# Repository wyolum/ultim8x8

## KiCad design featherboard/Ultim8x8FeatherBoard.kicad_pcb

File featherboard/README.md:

An add-on board to the Ultim8x8 LED Matrix for mounting an Adafruit Feather 
Huzzah (ESP8266).

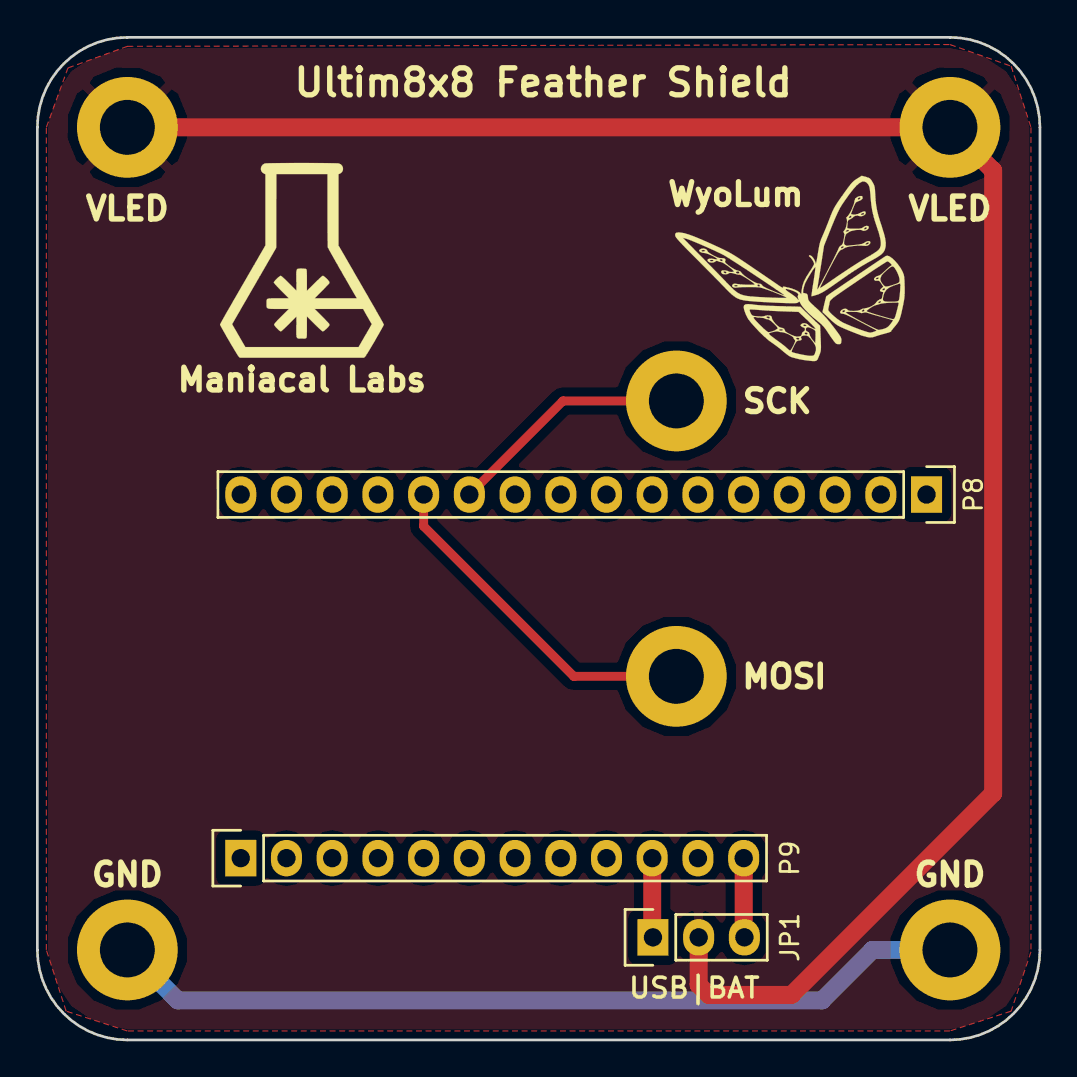
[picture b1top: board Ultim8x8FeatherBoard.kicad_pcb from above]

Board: 2 copper layers, 55.7 x 55.7 mm, 11 parts (0 on the bottom side), 6 nets.

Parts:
JP1: JUMPER3; Pin_Header_Straight_1x03
P1: Maniacal Labs; logo_MLlabs
P2, P3: VLED; Screw
P4, P5: GND; Screw
P6: MOSI; Screw
P7: SCK; Screw
P8: CONN_01X16; Pin_Header_Straight_1x16
P9: CONN_01X12; Pin_Header_Straight_1x12
P10: WyoLum; logo_wyo_butterfly

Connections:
GND: P4.1, P5.1, P8.4
MOSI: P6.1, P8.12
SCK: P7.1, P8.11
VBAT: JP1.3, P9.12
VLED: JP1.2, P2.1, P3.1
VUSB: JP1.1, P9.10

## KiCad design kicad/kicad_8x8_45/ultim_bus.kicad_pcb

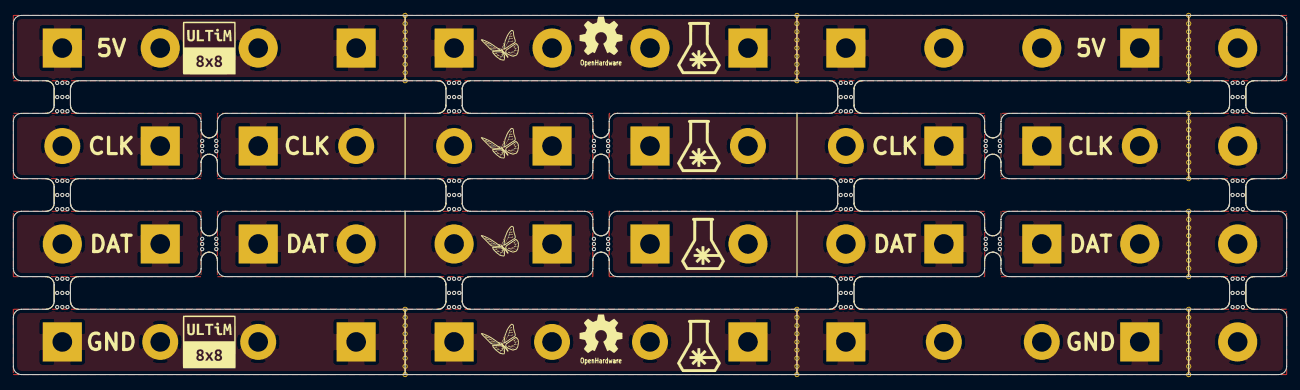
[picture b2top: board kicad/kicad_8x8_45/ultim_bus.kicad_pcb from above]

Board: 2 copper layers, 198.1 x 55.9 mm, 82 parts (0 on the bottom side), 10 nets.

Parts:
L1, L2: OSHW; OSHW_6mm
L3, L4, L5, L6: WyoLum; logo_wyo_butterfly_small
L7, L8, L9, L10: Maniacal; logo_MLlabs_small
L11, L12: ULTiM; logo_ultim8x8_small
M1, M2, M3, M4, M8, M9, M10, M11, M15, M16, M17, M18: MouseBite; mouse-bite-5.08mm-slot
M5, M6, M7, M12, M13, M14: MouseBite; mouse-bite-2.54mm-slot
P1, P4, P5, P8, P9, P12, P15, P16, P19, P20, P23, P24, P28, P29, P32, P33, P36, P37, P40, P43, P44, P47, P48, P51: CONN_1; Screw_SqPad
P2, P3, P6, P7, P10, P11, P13, P14, P17, P18, P21, P22, P25, P26, P27, P30, P31, P34, P35, P38, P39, P41, P42, P45, P46, P49, P50, P52: CONN_1; Screw

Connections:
/ROW1: P1.1, P2.1, P3.1, P4.1, P5.1, P6.1, P7.1, P8.1, P9.1, P10.1, P11.1, P12.1, P13.1
/ROW2: P40.1, P41.1, P42.1, P43.1, P44.1, P45.1, P46.1, P47.1, P48.1, P49.1, P50.1, P51.1, P52.1
/ROW31: P14.1, P15.1
/ROW32: P16.1, P17.1, P18.1, P19.1
/ROW33: P20.1, P21.1, P22.1, P23.1
/ROW34: P24.1, P25.1, P26.1
/ROW41: P27.1, P28.1
/ROW42: P29.1, P30.1, P31.1, P32.1
/ROW43: P33.1, P34.1, P35.1, P36.1
/ROW44: P37.1, P38.1, P39.1

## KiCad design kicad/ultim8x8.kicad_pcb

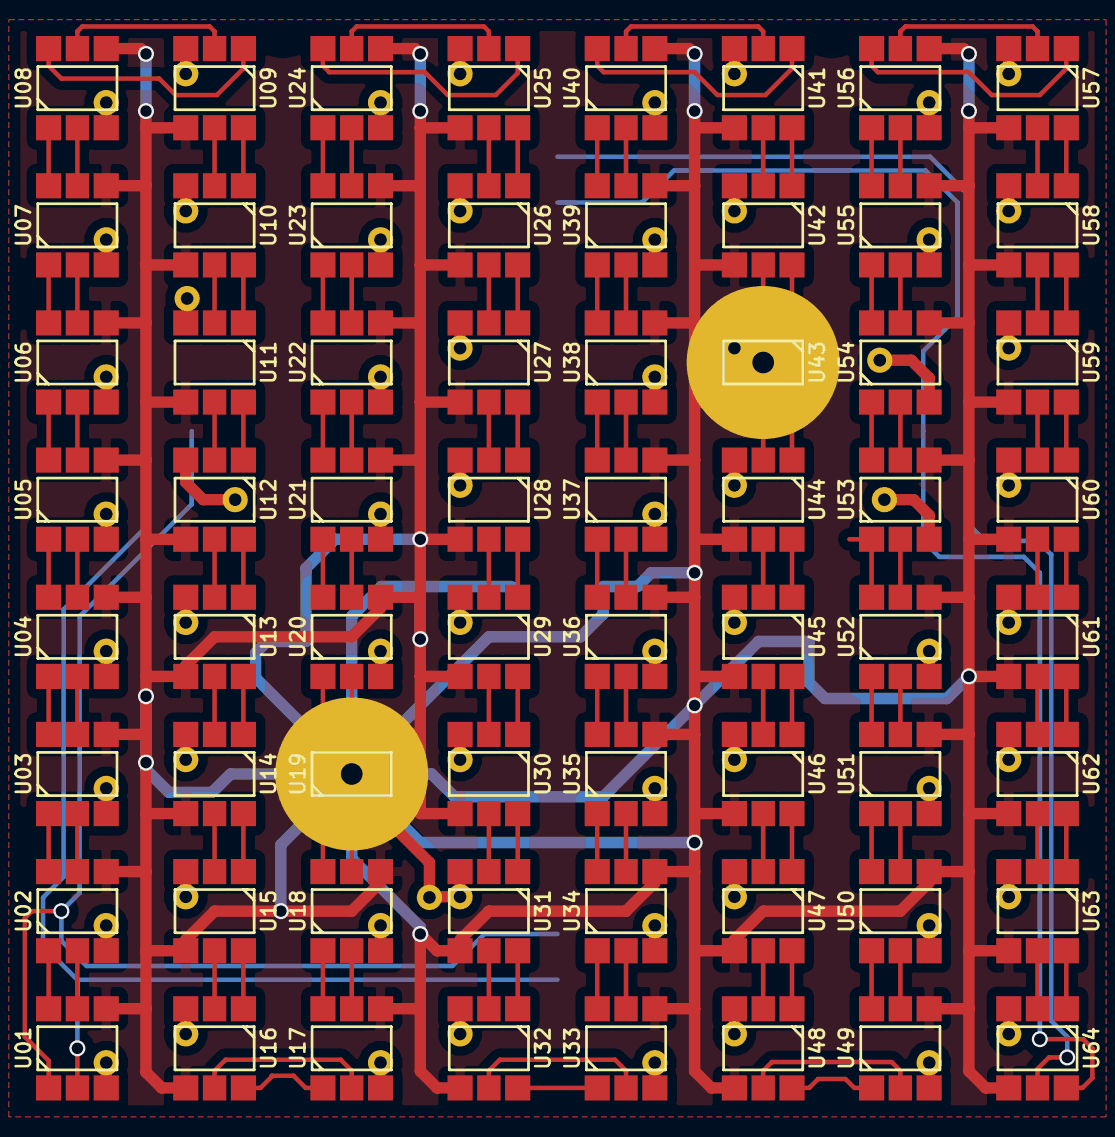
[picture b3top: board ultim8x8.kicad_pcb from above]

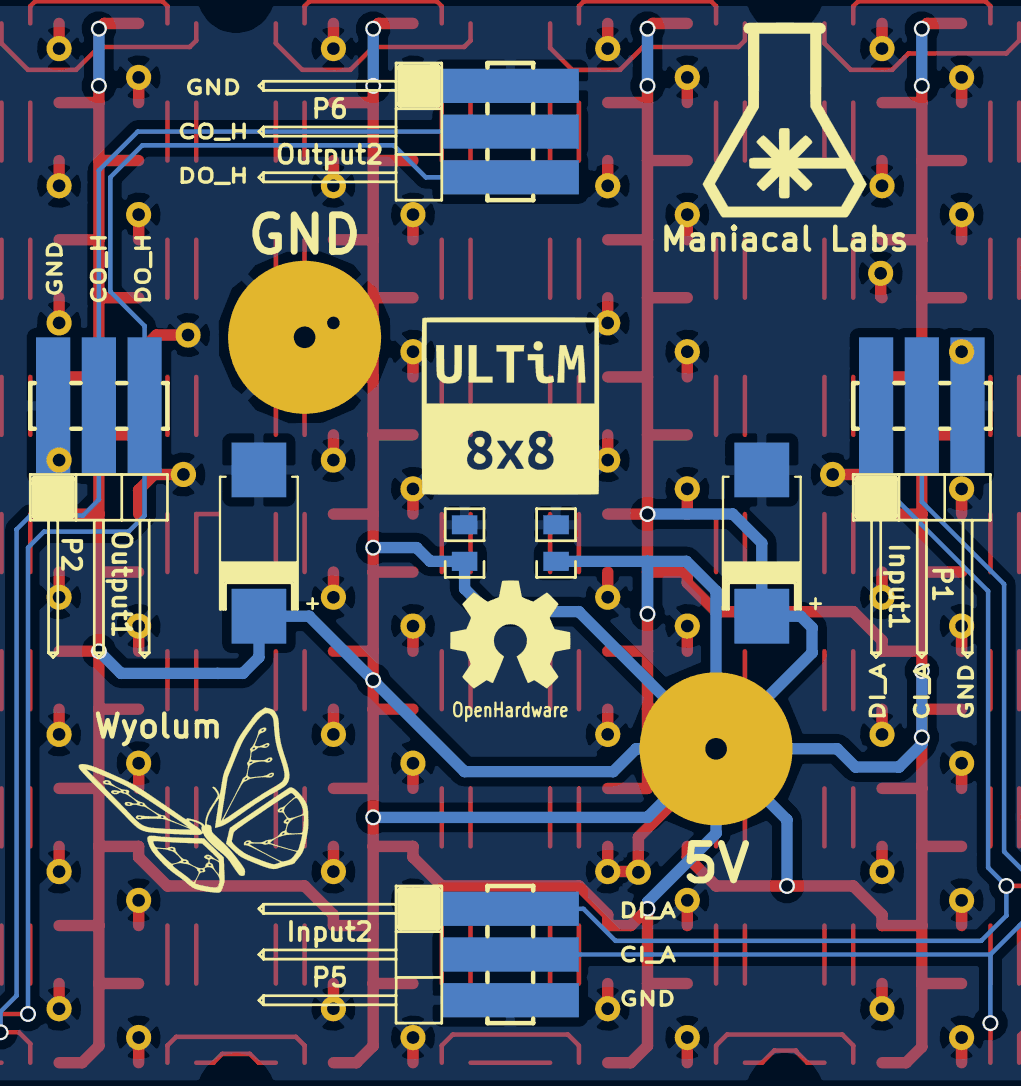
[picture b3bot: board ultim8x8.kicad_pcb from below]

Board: 2 copper layers, 78 parts (14 on the bottom side), 132 nets.

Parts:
C1, C3: 100nF; c_0805
C2: 47uF 20V; c_2917
C4: 47uF 8V; c_2917
L1: ULTiM8x8; logo_ultim8x8
L2: OSHW; OSHW_6mm
L3: Wyolum; logo_wyo_butterfly
L4: Maniacal Labs; logo_MLlabs
P1: Input1; header_3pos_smd_male
P2: Output1; header_3pos_smd_male
P3: 5V; PowerIn_stud
P4: GND; PowerIn_stud
P5: Input2; header_3pos_smd_male
P6: Output2; header_3pos_smd_male
U01, U02, U03, U04, U05, U06, U07, U08, U09, U10, U11, U12, U13, U14, U15, U16, U17, U18, U19, U20, U21, U22, U23, U24, U25, U26, U27, U28, U29, U30, U31, U32, U33, U34, U35, U36, U37, U38, U39, U40, U41, U42, U43, U44, U45, U46, U47, U48, U49, U50, U51, U52, U53, U54, U55, U56, U57, U58, U59, U60, U61, U62, U63, U64: APA102

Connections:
/Row_A/5V: C1.2, C2.1, C3.2, C4.1, P3.1, U01.4, U02.4, U03.4, U04.4, U05.4, U06.4, U07.4, U08.4, U09.4, U10.4, U11.4, U12.4, U13.4, U14.4, U15.4, U16.4, U17.4, U18.4, U19.4, U20.4, U21.4, U22.4, U23.4, U24.4, U25.4, U26.4, U27.4, U28.4, U29.4, U30.4, U31.4, U32.4, U33.4, U34.4, U35.4, U36.4, U37.4, U38.4, U39.4, U40.4, U41.4, U42.4, U43.4, U44.4, U45.4, U46.4, U47.4, U48.4, U49.4, U50.4, U51.4, U52.4, U53.4, U54.4, U55.4, U56.4, U57.4, U58.4, U59.4, U60.4, U61.4, U62.4, U63.4, U64.4
/Row_A/CI_A: P1.2, P5.2, U01.2
/Row_A/CI_B: U08.5, U09.2
/Row_A/DI_A: P1.1, P5.1, U01.1
/Row_A/DI_B: U08.6, U09.1
/Row_B/CI_C: U16.5, U17.2
/Row_B/DI_C: U16.6, U17.1
/Row_C/CI_D: U24.5, U25.2
/Row_C/DI_D: U24.6, U25.1
/Row_D/CI_E: U32.5, U33.2
/Row_D/DI_E: U32.6, U33.1
/Row_E/CI_F: U40.5, U41.2
/Row_E/DI_F: U40.6, U41.1
/Row_F/CI_G: U48.5, U49.2
/Row_F/DI_G: U48.6, U49.1
/Row_G/CI_H: U56.5, U57.2
/Row_G/DI_H: U56.6, U57.1
/Row_H/CO_H: P2.2, P6.2, U64.5
/Row_H/DO_H: P2.3, P6.3, U64.6
GND: C1.1, C2.2, C3.1, C4.2, P1.3, P2.1, P4.1, P5.3, P6.1, U01.3, U02.3, U03.3, U04.3, U05.3, U06.3, U07.3, U08.3, U09.3, U10.3, U11.3, U12.3, U13.3, U14.3, U15.3, U16.3, U17.3, U18.3, U19.3, U20.3, U21.3, U22.3, U23.3, U24.3, U25.3, U26.3, U27.3, U28.3, U29.3, U30.3, U31.3, U32.3, U33.3, U34.3, U35.3, U36.3, U37.3, U38.3, U39.3, U40.3, U41.3, U42.3, U43.3, U44.3, U45.3, U46.3, U47.3, U48.3, U49.3, U50.3, U51.3, U52.3, U53.3, U54.3, U55.3, U56.3, U57.3, U58.3, U59.3, U60.3, U61.3, U62.3, U63.3, U64.3
unnamed: U01.5, U02.2
unnamed: U01.6, U02.1
unnamed: U02.5, U03.2
unnamed: U02.6, U03.1
unnamed: U03.5, U04.2
unnamed: U03.6, U04.1
unnamed: U04.5, U05.2
unnamed: U04.6, U05.1
unnamed: U05.5, U06.2
unnamed: U05.6, U06.1
unnamed: U06.5, U07.2
unnamed: U06.6, U07.1
unnamed: U07.5, U08.2
unnamed: U07.6, U08.1
unnamed: U09.5, U10.2
unnamed: U09.6, U10.1
unnamed: U10.5, U11.2
unnamed: U10.6, U11.1
unnamed: U11.5, U12.2
unnamed: U11.6, U12.1
unnamed: U12.5, U13.2
unnamed: U12.6, U13.1
unnamed: U13.5, U14.2
unnamed: U13.6, U14.1
unnamed: U14.5, U15.2
unnamed: U14.6, U15.1
unnamed: U15.5, U16.2
unnamed: U15.6, U16.1
unnamed: U17.5, U18.2
unnamed: U17.6, U18.1
unnamed: U18.5, U19.2
unnamed: U18.6, U19.1
unnamed: U19.5, U20.2
unnamed: U19.6, U20.1
unnamed: U20.5, U21.2
unnamed: U20.6, U21.1
unnamed: U21.5, U22.2
unnamed: U21.6, U22.1
unnamed: U22.5, U23.2
unnamed: U22.6, U23.1
unnamed: U23.5, U24.2
unnamed: U23.6, U24.1
unnamed: U25.5, U26.2
unnamed: U25.6, U26.1
unnamed: U26.5, U27.2
unnamed: U26.6, U27.1
unnamed: U27.5, U28.2
unnamed: U27.6, U28.1
unnamed: U28.5, U29.2
unnamed: U28.6, U29.1
unnamed: U29.5, U30.2
unnamed: U29.6, U30.1
unnamed: U30.5, U31.2
unnamed: U30.6, U31.1
unnamed: U31.5, U32.2
unnamed: U31.6, U32.1
unnamed: U33.5, U34.2
unnamed: U33.6, U34.1
unnamed: U34.5, U35.2
unnamed: U34.6, U35.1
unnamed: U35.5, U36.2
unnamed: U35.6, U36.1
unnamed: U36.5, U37.2
unnamed: U36.6, U37.1
unnamed: U37.5, U38.2
unnamed: U37.6, U38.1
unnamed: U38.5, U39.2
unnamed: U38.6, U39.1
unnamed: U39.5, U40.2
unnamed: U39.6, U40.1
unnamed: U41.5, U42.2
unnamed: U41.6, U42.1
unnamed: U42.5, U43.2
unnamed: U42.6, U43.1
unnamed: U43.5, U44.2
unnamed: U43.6, U44.1
unnamed: U44.5, U45.2
unnamed: U44.6, U45.1
unnamed: U45.5, U46.2
unnamed: U45.6, U46.1
unnamed: U46.5, U47.2
unnamed: U46.6, U47.1
unnamed: U47.5, U48.2
unnamed: U47.6, U48.1
unnamed: U49.5, U50.2
unnamed: U49.6, U50.1
unnamed: U50.5, U51.2
unnamed: U50.6, U51.1
unnamed: U51.5, U52.2
unnamed: U51.6, U52.1
unnamed: U52.5, U53.2
unnamed: U52.6, U53.1
unnamed: U53.5, U54.2
unnamed: U53.6, U54.1
unnamed: U54.5, U55.2
unnamed: U54.6, U55.1
unnamed: U55.5, U56.2
unnamed: U55.6, U56.1
unnamed: U57.5, U58.2
unnamed: U57.6, U58.1
unnamed: U58.5, U59.2
unnamed: U58.6, U59.1
unnamed: U59.5, U60.2
unnamed: U59.6, U60.1
unnamed: U60.5, U61.2
unnamed: U60.6, U61.1
unnamed: U61.5, U62.2
unnamed: U61.6, U62.1
unnamed: U62.5, U63.2
unnamed: U62.6, U63.1
unnamed: U63.5, U64.2
unnamed: U63.6, U64.1

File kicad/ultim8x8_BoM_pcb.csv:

"Id";"Designator";"Package";"Quantity";"Designation";"Supplier and ref";
1;"C3,C1";"c_0805";2;"100nF";;;
2;"P3";"PowerIn_stud";1;"5V";;;
3;"P4";"PowerIn_stud";1;"GND";;;
4;"L2";"OSHW_6mm";1;"OSHW";;;
5;"L4";"logo_MLlabs";1;"Maniacal Labs";;;
6;"L3";"logo_wyo_butterfly";1;"Wyolum";;;
7;"P6";"header_3pos_smd_male";1;"Output2";;;
8;"P5";"header_3pos_smd_male";1;"Input2";;;
9;"P2";"header_3pos_smd_male";1;"Output1";;;
10;"P1";"header_3pos_smd_male";1;"Input1";;;
11;"U04,U01,U02,U03,U05,U06,U07,U08,U09,U10,U11,U12,U13,U14,U15,U17,U18,U19,U20,U21,U22,U23,U24,U25,U26,U27,U28,U29,U30,U31,U32,U33,U34,U35,U36,U37,U38,U39,U40,U41,U42,U43,U44,U45,U46,U47,U48,U49,U50,U51,U52,U53,U54,U55,U56,U57,U58,U59,U60,U61,U62,U63,U64,U16";"APA102";64;"APA102";;;
12;"C2";"c_2917";1;"47uF 20V";;;
13;"C4";"c_2917";1;"47uF 8V";;;
14;"L1";"logo_ultim8x8";1;"ULTiM8x8";;;

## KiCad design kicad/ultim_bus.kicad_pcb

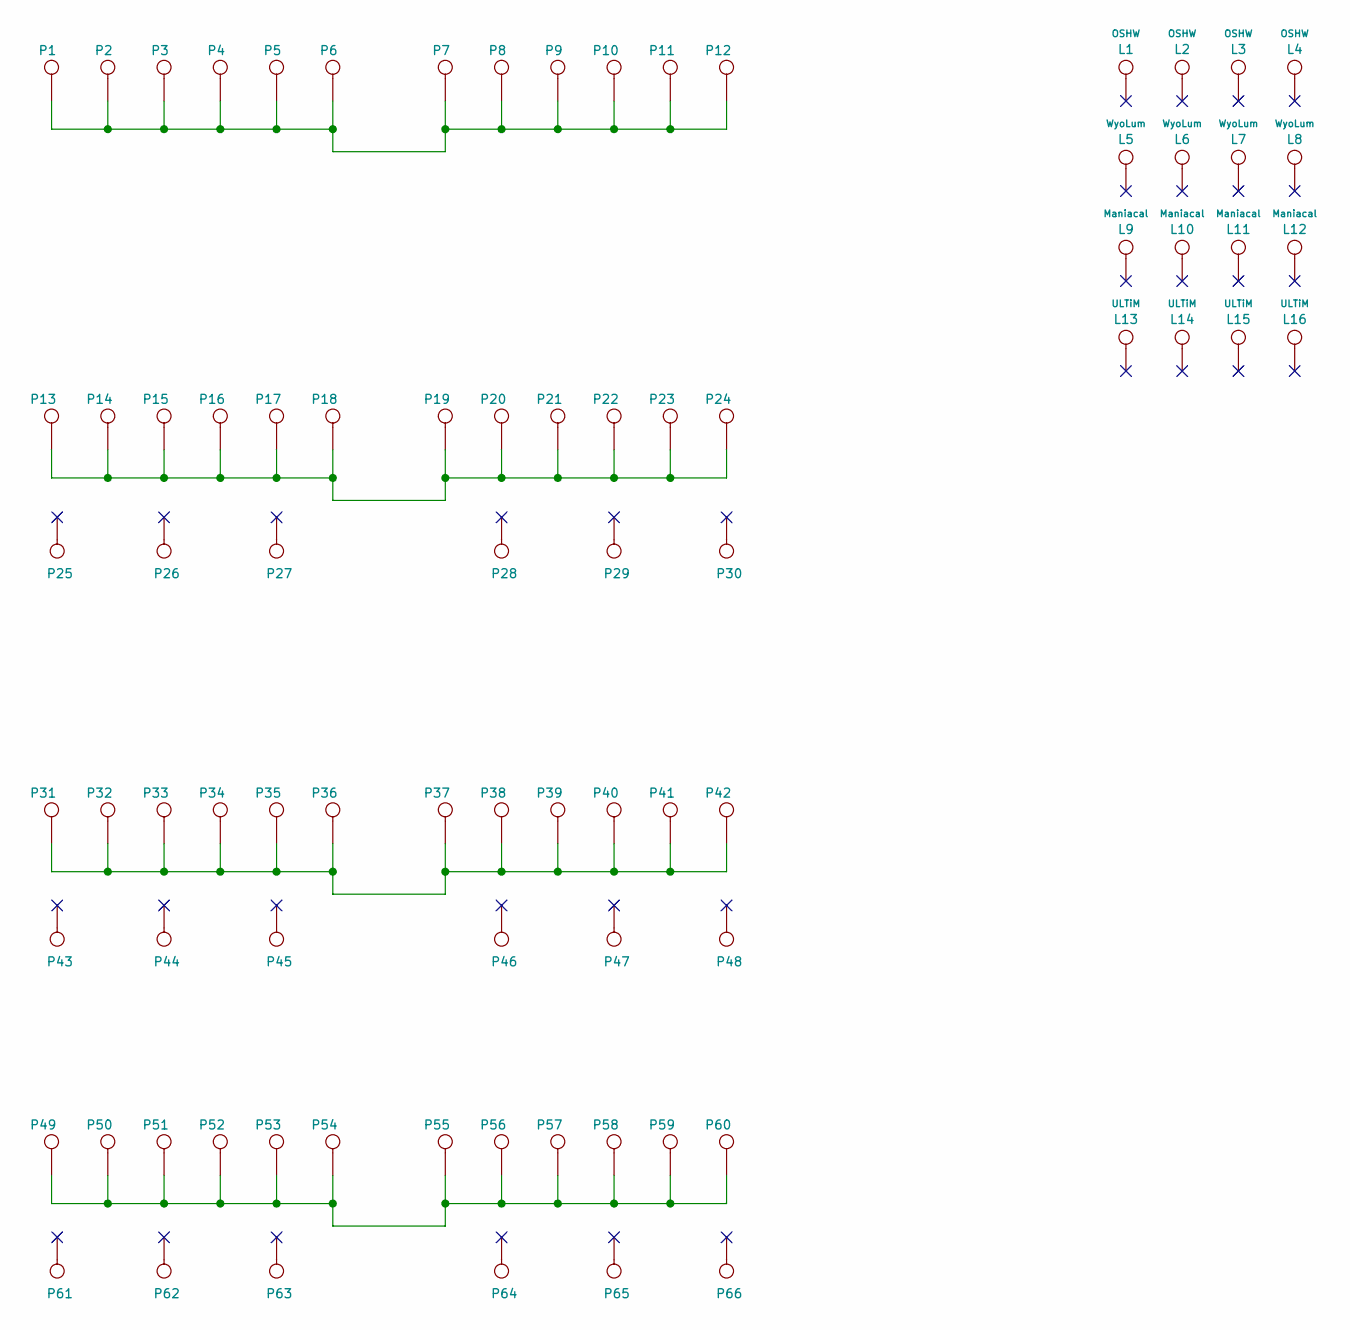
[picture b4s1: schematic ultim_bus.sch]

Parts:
L1, L2, L3, L4: OSHW; OSHW_6mm
L5, L6, L7, L8: WyoLum; logo_wyo_butterfly_small
L9, L10, L11, L12: Maniacal; logo_MLlabs_small
L13, L14, L15, L16: ULTiM; logo_ultim8x8_small
P1, P2, P3, P4, P5, P6, P7, P8, P9, P10, P11, P12, P13, P14, P15, P16, P17, P18, P19, P20, P21, P22, P23, P24, P25, P26, P27, P28, P29, P30, P31, P32, P33, P34, P35, P36, P37, P38, P39, P40, P41, P42, P43, P44, P45, P46, P47, P48, P49, P50, P51, P52, P53, P54, P55, P56, P57, P58, P59, P60, P61, P62, P63, P64, P65, P66: CONN_1; Screw

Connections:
/ROW1: P1.1, P2.1, P3.1, P4.1, P5.1, P6.1, P7.1, P8.1, P9.1, P10.1, P11.1, P12.1; also elsewhere on the board
/ROW2: P13.1, P14.1, P15.1, P16.1, P17.1, P18.1, P19.1, P20.1, P21.1, P22.1, P23.1, P24.1; also elsewhere on the board
/ROW3: P31.1, P32.1, P33.1, P34.1, P35.1, P36.1, P37.1, P38.1, P39.1, P40.1, P41.1, P42.1; also elsewhere on the board
/ROW4: P49.1, P50.1, P51.1, P52.1, P53.1, P54.1, P55.1, P56.1, P57.1, P58.1, P59.1, P60.1; also elsewhere on the board

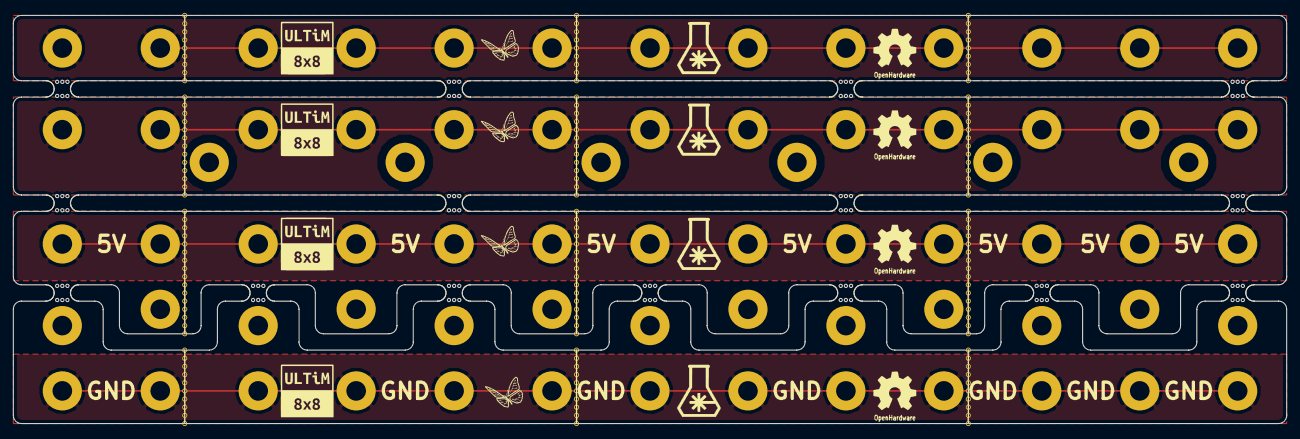
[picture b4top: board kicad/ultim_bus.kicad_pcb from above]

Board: 2 copper layers, 198.1 x 63.5 mm, 102 parts (0 on the bottom side), 4 nets.

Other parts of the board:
M1, M2, M3, M4, M5, M6, M7, M8, M9, M10, M11, M12, M13, M14, M15: MouseBite; mouse-bite-2.54mm-slot
P67, P68, P69, P70, P71: CONN_1; Screw

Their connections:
/ROW1: P67.1; also elsewhere on the board
/ROW2: P68.1; also elsewhere on the board
/ROW3: P69.1; also elsewhere on the board
/ROW4: P70.1; also elsewhere on the board

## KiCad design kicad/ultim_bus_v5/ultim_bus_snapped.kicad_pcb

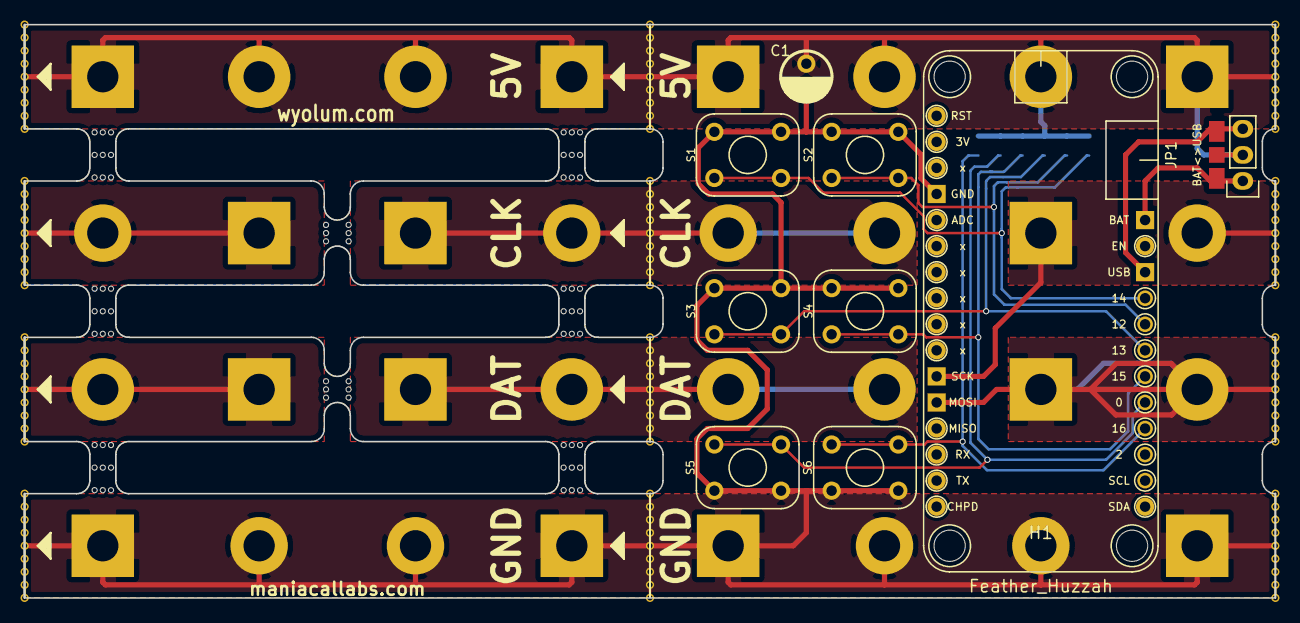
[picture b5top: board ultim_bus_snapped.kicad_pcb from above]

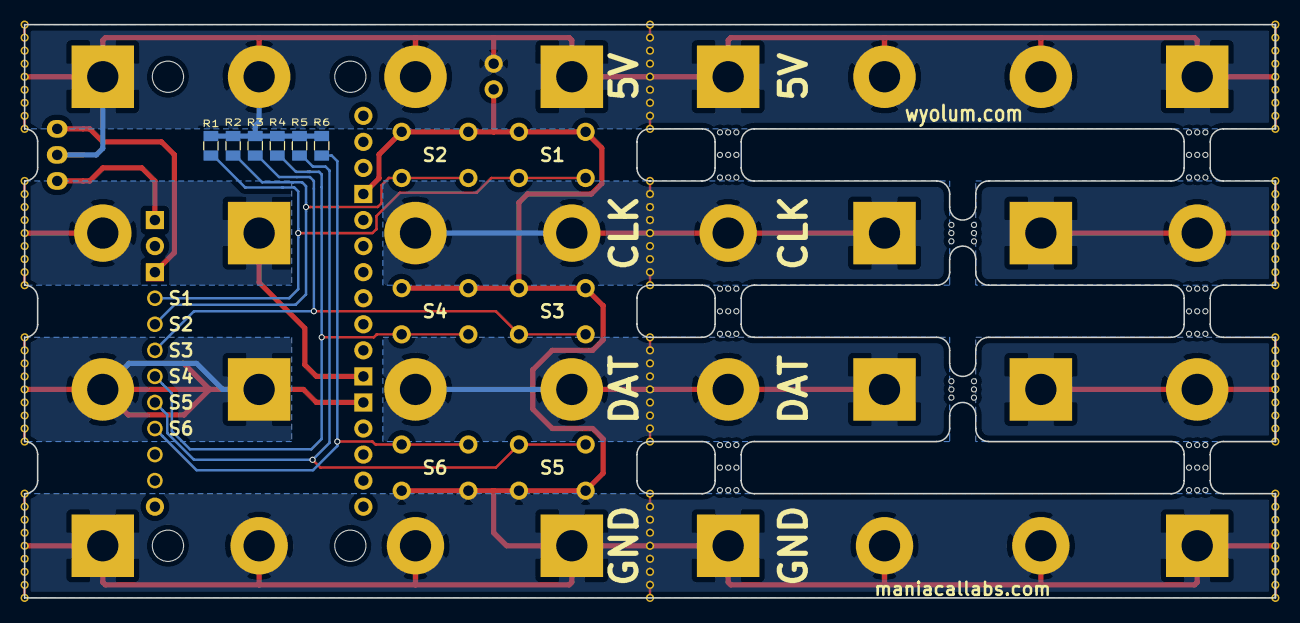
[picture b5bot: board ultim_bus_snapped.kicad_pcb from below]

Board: 2 copper layers, 121.9 x 55.9 mm, 67 parts (6 on the bottom side), 16 nets.

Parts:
C1: 470uF 10V; cap_pol_rad3
H1: Feather_Huzzah; FEATHER_Huzzah
JP1: PWR_SEL; switch_spdt
M3, M4, M10, M11, M17, M18: MouseBite; mouse-bite-5.08mm-slot
M6, M13: MouseBite; mouse-bite-2.54mm-slot
P5, P8, P9, P12, P19, P20, P23, P24, P32, P33, P36, P37, P44, P47, P48, P51: CONN_1; Screw_SqPad
P6, P7, P10, P11, P18, P21, P22, P25, P31, P34, P35, P38, P45, P46, P49, P50: CONN_1; Screw
R1, R2, R3, R4, R5, R6: 10k; r_0805
S1, S2, S3, S4, S5, S6: SPST-M-2; SW-PB
v1, v2, v3, v4, v5, v6, v7, v8, v9, v10, v11, v12: via_0.8x9

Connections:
/5V: C1.1, JP1.2, P5.1, P6.1, P7.1, P8.1, P9.1, P10.1, P11.1, P12.1, R1.2, R2.2, R3.2, R4.2, R5.2, R6.2, v1.1, v1.2, v1.3, v1.4, v1.5, v1.6, v1.7, v1.8, v1.9, v2.1, v2.2, v2.3, v2.4, v2.5, v2.6, v2.7, v2.8, v2.9, v3.1, v3.2, v3.3, v3.4, v3.5, v3.6, v3.7, v3.8, v3.9
/CLK: H1.23, P24.1, P25.1, v7.1, v7.2, v7.3, v7.4, v7.5, v7.6, v7.7, v7.8, v7.9
/CLK1: P20.1, P21.1, P22.1, P23.1, v8.1, v8.2, v8.3, v8.4, v8.5, v8.6, v8.7, v8.8, v8.9
/CLK2: P18.1, P19.1, v9.1, v9.2, v9.3, v9.4, v9.5, v9.6, v9.7, v9.8, v9.9
/DAT: H1.24, P37.1, P38.1, v10.1, v10.2, v10.3, v10.4, v10.5, v10.6, v10.7, v10.8, v10.9
/DAT1: P33.1, P34.1, P35.1, P36.1, v11.1, v11.2, v11.3, v11.4, v11.5, v11.6, v11.7, v11.8, v11.9
/DAT2: P31.1, P32.1, v12.1, v12.2, v12.3, v12.4, v12.5, v12.6, v12.7, v12.8, v12.9
/GND: C1.2, H1.16, P44.1, P45.1, P46.1, P47.1, P48.1, P49.1, P50.1, P51.1, S1.2, S2.2, S3.2, S4.2, S5.2, S6.2, v4.1, v4.2, v4.3, v4.4, v4.5, v4.6, v4.7, v4.8, v4.9, v5.1, v5.2, v5.3, v5.4, v5.5, v5.6, v5.7, v5.8, v5.9, v6.1, v6.2, v6.3, v6.4, v6.5, v6.6, v6.7, v6.8, v6.9
/S1: H1.9, R1.1, S1.1
/S2: H1.8, R2.1, S2.1
/S3: H1.7, R3.1, S3.1
/S4: H1.6, R4.1, S4.1
/S5: H1.5, R5.1, S5.1
/S6: H1.4, R6.1, S6.1
/VBAT: H1.12, JP1.1
/VUSB: H1.10, JP1.3
